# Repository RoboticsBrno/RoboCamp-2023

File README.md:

# Robotický tábor

## Vítej na stránkách Robotického tábora 2023

<!-- <div align="center">
    <table>
        <tr>
            <td></td>
            <td></td>
            <td></td>
        </tr>
        <tr>
            <td style="text-align: center;"><a href="https://2022.robotickytabor.cz/roboSvit/">RoboSvit</a></td>
            <td style="text-align: center;"><a href="https://2022.robotickytabor.cz/hradla/">Hradla</a></td>
            <td style="text-align: center;"><a href="https://2022.robotickytabor.cz/electronicDie/">Hrací kostka</a></td>
        </tr>
        <tr>
            <td></td>
            <td></td>
            <td></td>
        </tr>
        <tr>
            <td style="text-align: center;"><a href="https://2022.robotickytabor.cz/solderingChallenge/">Pájecí výzva</a></td>
            <td style="text-align: center;"><a href="https://2022.robotickytabor.cz/blackBox/">BlackBox</a></td>
            <td style="text-align: center;"><a href="https://2022.robotickytabor.cz/electron/">Electron</a></td>
        </tr>
        <tr>
            <td></td>
            <td></td>
            <td></td>
        </tr>
        <tr>
            <td style="text-align: center;"><a href="https://2022.robotickytabor.cz/beamBot/">Beam bot</a></td>
            <td style="text-align: center;"><a href="https://2022.robotickytabor.cz/microbit/">MicroBit</a></td>
            <td style="text-align: center;"><a href="https://2022.robotickytabor.cz/microJuice/">MicroJuice</a></td>
        </tr>
        <tr>
            <td></td>
            <td></td>
            <td></td>
        </tr>
        <tr>
            <td style="text-align: center;"><a href="https://2022.robotickytabor.cz/microbit/">MicroBit</a></td>
            <td style="text-align: center;"><a href="https://2022.robotickytabor.cz/microJuice/">MicroJuice</a></td>
            <td></td>
        </tr>
    </table>
</div> -->

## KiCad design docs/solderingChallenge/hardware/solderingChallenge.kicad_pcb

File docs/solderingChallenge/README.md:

# O co jde?

Pájecí výzva obsahuje jeden relativně jednoduchý obvod založený na populárním
integrovaném obvodu 555. Pokud se ti podaří správně zapájet všechny součástky, tak po zapojení do USB portu začne LED blikat s frekvencí cca 2 Hz.

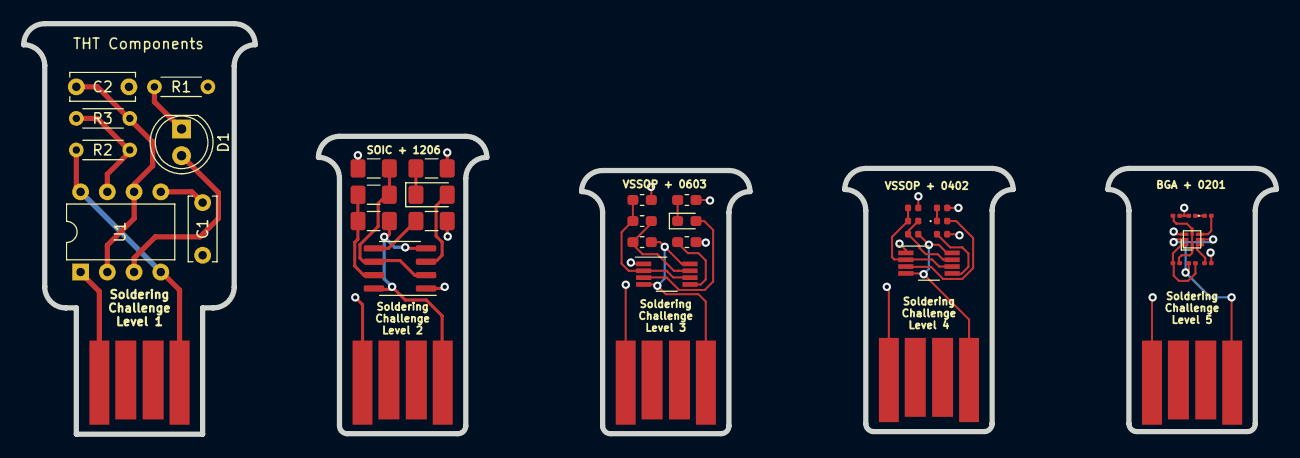
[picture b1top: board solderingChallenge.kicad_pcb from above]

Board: 2 copper layers, 119.0 x 39.0 mm, 40 parts (0 on the bottom side), 35 nets.

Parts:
C1: 10n; C_Disc_D6.0mm_W2.5mm_P5.00mm
C2: 4.7u; C_Disc_D6.0mm_W2.5mm_P5.00mm
C3: 10n; C_1206_3216Metric_Pad1.42x1.75mm_HandSolder
C4: 4.7u; C_1206_3216Metric_Pad1.42x1.75mm_HandSolder
C5: 10n; C_0603_1608Metric_Pad1.05x0.95mm_HandSolder
C6: 4.7u; C_0603_1608Metric_Pad1.05x0.95mm_HandSolder
C7: 10n; C_0402_1005Metric
C8: 4.7u; C_0402_1005Metric
C9: 10n; C_0201_0603Metric
C10: 4.7u; C_0201_0603Metric
D1: LED; LED_D5.0mm
D2: LED; LED_1206_3216Metric_Pad1.42x1.75mm_HandSolder
D3: LED; LED_0603_1608Metric_Pad1.05x0.95mm_HandSolder
D4: LED; LED_0402_1005Metric
D5: LED; LED_0201_0603Metric
J2, J4, J6, J8, J10: USB_A; usb-PCB
R1: 330R; R_Axial_DIN0204_L3.6mm_D1.6mm_P5.08mm_Horizontal
R2: 10k; R_Axial_DIN0204_L3.6mm_D1.6mm_P5.08mm_Horizontal
R3: 100k; R_Axial_DIN0204_L3.6mm_D1.6mm_P5.08mm_Horizontal
R4: 330R; R_1206_3216Metric_Pad1.42x1.75mm_HandSolder
R5: 10k; R_1206_3216Metric_Pad1.42x1.75mm_HandSolder
R6: 100k; R_1206_3216Metric_Pad1.42x1.75mm_HandSolder
R7: 330R; R_0603_1608Metric_Pad1.05x0.95mm_HandSolder
R8: 10k; R_0603_1608Metric_Pad1.05x0.95mm_HandSolder
R9: 100k; R_0603_1608Metric_Pad1.05x0.95mm_HandSolder
R10: 330R; R_0402_1005Metric
R11: 10k; R_0402_1005Metric
R12: 100k; R_0402_1005Metric
R13: 330R; R_0201_0603Metric
R14: 10k; R_0201_0603Metric
R15: 100k; R_0201_0603Metric
U1: LM555xN; DIP-8_W7.62mm
U2: LMC555xM; SOIC-8_3.9x4.9mm_P1.27mm
U3, U4: LMC555xMM; VSSOP-8_3.0x3.0mm_P0.65mm
U5: LMC555xTP; Texas_DSBGA-8_1.43x1.41mm_Layout3x3_P0.5mm

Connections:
/Level 1 - THT/GND: C1.2, C2.2, J2.4, R1.1, U1.1
/Level 1 - THT/VCC: J2.1, R2.1, U1.4, U1.8
/Level 2 - 1206/GND: C3.2, C4.2, J4.4, R4.1, U2.1
/Level 2 - 1206/VCC: J4.1, R5.1, U2.4, U2.8
/Level 3 - 0603/GND: C5.2, C6.2, J6.4, R7.1, U3.1
/Level 3 - 0603/VCC: J6.1, R8.1, U3.4, U3.8
/Level 4 - 0402/GND: C7.2, C8.2, J8.4, R10.1, U4.1
/Level 4 - 0402/VCC: J8.1, R11.1, U4.4, U4.8
/Level 5 - 0201/GND: C9.2, C10.2, J10.4, R13.1, U5.A3
/Level 5 - 0201/VCC: J10.1, R14.1, U5.A2, U5.C2
unnamed: C1.1, U1.5
unnamed: C2.1, R3.2, U1.2, U1.6
unnamed: C3.1, U2.5
unnamed: C4.1, R6.2, U2.2, U2.6
unnamed: C5.1, U3.5
unnamed: C6.1, R9.2, U3.2, U3.6
unnamed: C7.1, U4.5
unnamed: C8.1, R12.2, U4.2, U4.6
unnamed: C9.1, U5.C1
unnamed: C10.1, R15.2, U5.B1, U5.B3
unnamed: D1.1, R1.2
unnamed: D1.2, U1.3
unnamed: D2.1, R4.2
unnamed: D2.2, U2.3
unnamed: D3.1, R7.2
unnamed: D3.2, U3.3
unnamed: D4.1, R10.2
unnamed: D4.2, U4.3
unnamed: D5.1, R13.2
unnamed: D5.2, U5.C3
unnamed: R2.2, R3.1, U1.7
unnamed: R5.2, R6.1, U2.7
unnamed: R8.2, R9.1, U3.7
unnamed: R11.2, R12.1, U4.7
unnamed: R14.2, R15.1, U5.A1

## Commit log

2023-06-13 Init page commit
2023-06-13 Add team
2023-06-13 Add blink example
2023-06-30 Add sponsors, update actions
2023-06-30 Add style
2023-07-04 Add useful plugins
2023-07-05 Add old gadgets + jaculus
2023-07-05 Install Jaculus
2023-07-05 Update jaculuc install manual
2023-07-05 add example1
2023-07-05 Add drone setup
2023-07-05 Add dummy text
2023-07-05 Add elks lectures
2023-07-05 chore: added extension image
2023-07-06 Add notes to lecture 1
2023-07-06 added lesson 2
    Added lesson 2 completed with examples of code.
2023-07-06 Add dev guide
2023-07-06 lecture3: draft
2023-07-06 Wrote most of lesson 5
2023-07-06 Add docker image for drone
2023-07-06 fixed typeos in lecture 1
2023-07-06 Update '.drone.yml'
2023-07-06 Add typedoc documentation
2023-07-06 lecture4: wip
2023-07-06 Update 'Dockerfile'
2023-07-06 lessons 1 - 5 update
2023-07-06 lesson 2 event -> událost
2023-07-06 Fix typedoc
2023-07-06 pins defined using const
2023-07-06 lecture3: edits
2023-07-06 lectures: add color library
2023-07-06 lesson 1 and 2 update
    Lesson 1: changed example + edited "Úprava programu" chapter
    Lesson : pin definitions names changed
2023-07-06 lecture4: draft
2023-07-06 feat: added lection 6
2023-07-07 lesson 2: INPUT -> INPUT_PULLUP
2023-07-07 Lesson 2: added usage of colors.js
2023-07-07 lectures: fix typos and consistency
2023-07-07 Add new plugins
2023-07-07 Lesson 1: usage of colors.js
2023-07-07 Lesson 2: added colors. js to blank_Project
2023-07-07 Add zip files
2023-07-07 Add zip plugin runner
2023-07-07 Upgrade typedoc plugin
2023-07-07 Add debug printout
2023-07-07 Upgrade zip folder plugin to fix build
2023-07-07 Remove debug printout
2023-07-07 Add links to zip
2023-07-07 Add large zip buttons
2023-07-07 Add color libs
2023-07-07 Update images, fix colors
2023-07-07 fix: typos
2023-07-07 feat: added example 6
2023-07-07 added lesson 7 - ADC
2023-07-07 Fix lectures neopixel, codes
2023-07-07 Fix lectures 4, 5
2023-07-07 Fix lecture 6, change bar image
2023-07-07 lecture5: update
2023-07-07 lectures: update pin number for ledstrip
2023-07-07 Update lecture 6
2023-07-07 lecture?: add array exercies, separate string
2023-07-07 lectures: switch 6 and 7
2023-07-07 lecture3: add empty project
2023-07-07 lecture4: add skeleton
2023-07-08 lectures6-8: updates
2023-07-08 Add demo project, updated pins image
2023-07-08 Add pin cfg
2023-07-08 Add new ELKS images
2023-07-08 lectures: add example solutions
2023-07-08 lectures: add index.ts to solutions
2023-07-09 hide string lecture until finished
2023-07-09 lectures: update button pin
2023-07-09 Add robosvit
2023-07-09 Fix color
2023-07-09 Fix typo
2023-07-09 lecture2: add intro
2023-07-09 Upgrade to new zip plugin version
2023-07-09 Add elks box manual
2023-07-10 reduce default brightness
2023-07-10 Add ELKS box to index
2023-07-10 lecture4: throw away async
2023-07-11 fix: typo
2023-07-11 Add Lekce9 - radio
2023-07-11 update type defs
2023-07-11 Add grafo
2023-07-11 Update types
2023-07-11 Fix lekce 4
2023-07-11 lecture8: finish string lecture
2023-07-11 lecture8: missing tick
2023-07-11 lecture8: broken link
2023-07-12 fix L1 polarity
2023-07-12 Fix name
2023-07-14 Added RoboPlace
2023-07-14 fix: locate picture
2023-07-15 Added lekce10 aka servo
2023-07-15 Added lecke10 aka servo
2023-07-18 Added how to install Jaculus to faq section
2023-07-28 Moved RoboPlace and added new instructions
2023-08-23 added RoboPlace section
2023-09-04 Update RoboPlace
    Updated roboplace informations (I rewrote the code)
2023-10-02 Fix local links, add more info - grafo
2023-10-02 Deployed cc7a9e6 with MkDocs version: 1.4.3
